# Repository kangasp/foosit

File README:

To deploy this thing:
  Log into heroku
    `heroku login`
  git push heroku master

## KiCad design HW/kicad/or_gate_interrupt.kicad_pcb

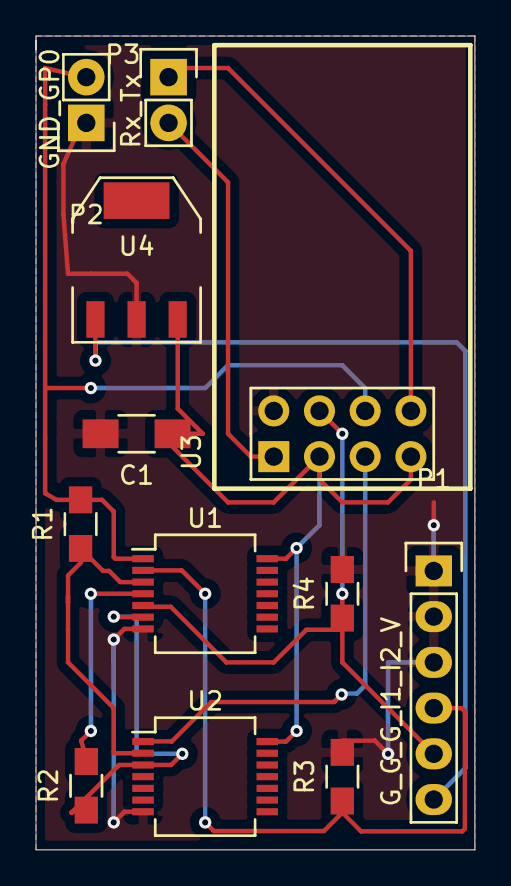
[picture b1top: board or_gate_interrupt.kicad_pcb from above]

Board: 2 copper layers, 24.4 x 45.2 mm, 12 parts (0 on the bottom side), 12 nets.

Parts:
C1: 100uF; C_1206_HandSoldering
P1: G_G_G_I1_I2_V; Pin_Header_Straight_1x06
P2: GND_GP0; Pin_Header_Straight_1x02
P3: Rx_Tx; Pin_Header_Straight_1x02
R1, R2, R3, R4: 1K; R_0805_HandSoldering
U1: 74LS32; SSOP-14_5.3x6.2mm_Pitch0.65mm
U2: 74HC02; SSOP-14_5.3x6.2mm_Pitch0.65mm
U3: ESP-01v090; ESP-01
U4: LT1129CST-3.3; SOT-223

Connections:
+3V3: C1.1, U1.14, U2.14, U3.3, U3.7, U4.3
GND: C1.2, P1.1, P1.2, P1.3, P2.1, R3.2, R4.2, U1.7, U2.7, U3.2, U4.2
unnamed: P1.4, R3.1, U1.2
unnamed: P1.5, R4.1, U1.5, U3.4
unnamed: P1.6, U4.1
unnamed: P2.2, R1.2, U1.1, U3.6
unnamed: P3.1, U3.8
unnamed: P3.2, U3.1
unnamed: R1.1, U1.3, U2.2
unnamed: R2.1, U1.6, U2.3
unnamed: R2.2, U1.4
unnamed: U2.1, U3.5

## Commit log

2016-08-30 First commit.
2016-08-30 Update proc file.
2016-08-30 Updating app.
2016-08-30 Update again.
2016-08-30 Update reqs.
2016-08-30 Adding readme instructions.
2016-08-31 Updated port etc.
2016-08-31 Add gitignore
2016-08-31 Updating to a more complex app.
2016-08-31 Add db.
2016-09-01 Updating again.
2016-09-02 Adding foosBox.ino arduino sketch.
2016-09-02 Moving sketch so arduino is happy.
2016-09-02 Added file things to think about.
2016-09-15 Proved the concept of the circuit for latching.
    Uses an OR gate with the input linked to the output.
    The input is then driven low by changing the reading pin
    to an output.
2016-09-15 Not sure if this thing works.
    Proved it with the other sketch.
2016-09-23 Adding HW design.
2016-09-24 Added a few parts.
2016-09-26 Updated a few layout things.
2016-09-28 Most of the routing done. Trying to figure out ground plane.
2016-09-28 Think layout is done for first pass.
2016-10-05 Updating layout.
2016-10-06 Adding BOM.
2016-10-06 Updated BOM. Changed cap to smt.
2016-10-07 Rerouted with new resistor size. Need to shrink board.
2016-10-07 Can't seem to change size of board.
2016-10-07 Added dimensions to drawing.
2016-10-10 Updated part numbers for BOM.
2016-10-11 Adding updated BOM.
2016-10-11 Updating some changes.
2016-10-11 Updating bom
2016-10-12 Sending this to the FAB, after opening and checking.
    V1
2016-10-12 Updating layer to silk, so can see what the pinouts are.
2016-10-20 Adding first battery footprint.
